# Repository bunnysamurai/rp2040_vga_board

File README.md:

# Intro
A modified version of the RP2040 vga support board from Raspberry Pi.

Source VGA board can be found [here](https://datasheets.raspberrypi.com/rp2040/VGA-KiCAD.zip).

As a design goal, this board is intended to support all the features made available from the [RP2040 DOOM](https://kilograham.github.io/rp2040-doom/) project:
- Keyboard input
- Full colour VGA
- Original(ish) sound
- Multiplayer (over I2C)

# Tools
KiCad: version 6.0.9, at least

Design rules follow [those documented by PCBWay](https://www.pcbway.com/capabilities.html)

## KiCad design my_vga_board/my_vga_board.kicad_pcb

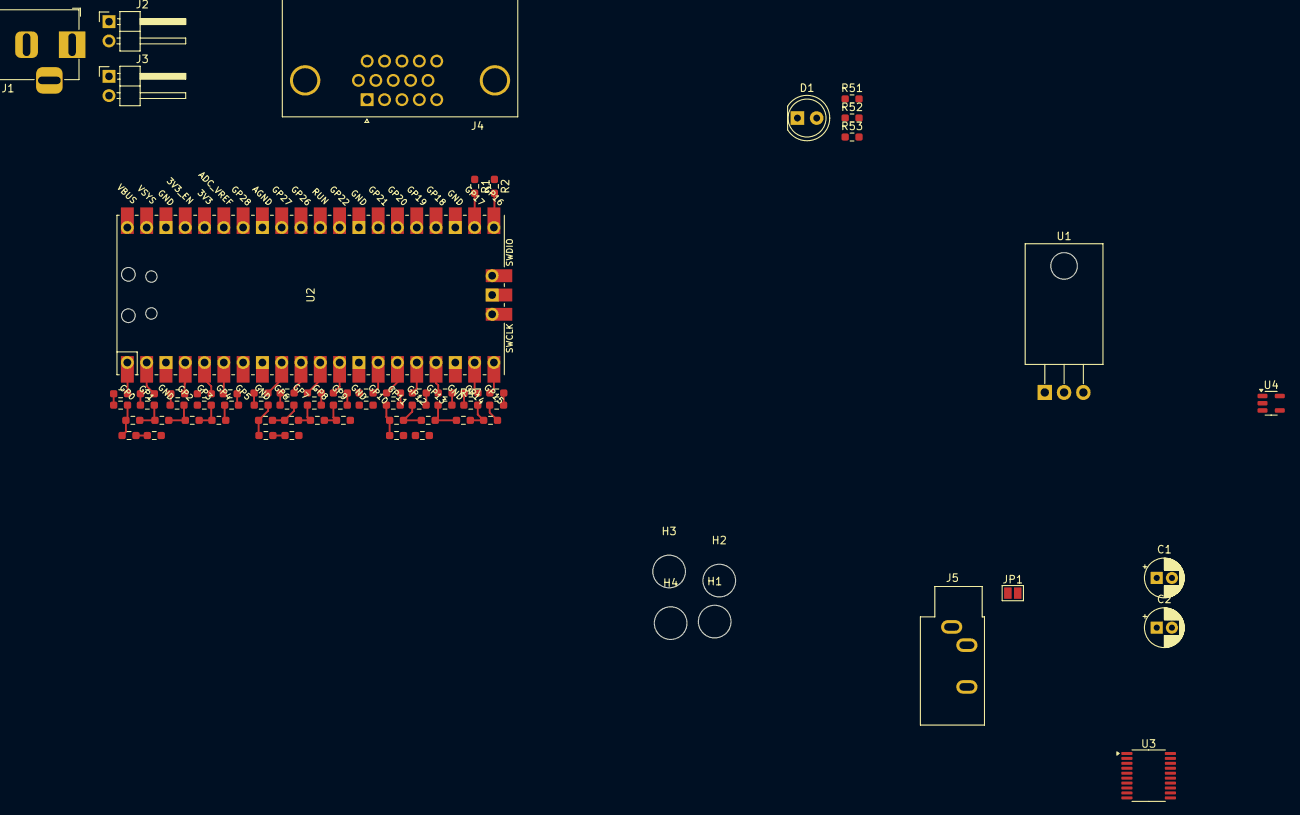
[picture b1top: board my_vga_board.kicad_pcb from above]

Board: 2 copper layers, 70 parts (0 on the bottom side), 67 nets.

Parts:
C1: 0.33uF; CP_Radial_D5.0mm_P2.00mm
C2: 0.1uF; CP_Radial_D5.0mm_P2.00mm
D1: LED; LED_D5.0mm
H1, H2, H3, H4: MountingHole; MountingHole_4.3mm_M4
J1: Barrel_Jack; BarrelJack_Horizontal
J2: I2C_A; PinHeader_1x02_P2.54mm_Horizontal
J3: I2C_B; PinHeader_1x02_P2.54mm_Horizontal
J4: L77HDE15SD1CH4F; DSUB-15-L77HDE15SD1CH4F
J5: AudioJack2_Ground; Jack_3.5mm_CUI_SJ1-3533NG_Horizontal
JP1: Open; SolderJumper-2_P1.3mm_Open_Pad1.0x1.5mm
R1, R2: 47; R_0603_1608Metric_Pad0.98x0.95mm_HandSolder
R3, R4, R5, R6, R7, R8, R9, R10, R11, R12, R13, R14, R15, R16, R17, R18, R19, R20, R21, R22, R23, R24, R25, R26, R27, R28, R29, R30, R31, R32, R33, R34, R35, R36, R37, R38, R39, R40, R41, R42, R43, R44, R45, R46, R47, R48, R49, R50: R; R_0603_1608Metric_Pad0.98x0.95mm_HandSolder
R51, R52: 470; R_0603_1608Metric_Pad0.98x0.95mm_HandSolder
R53: 330; R_0603_1608Metric_Pad0.98x0.95mm_HandSolder
U1: LM7805_TO220; TO-220-3_Horizontal_TabDown
U2: Pico; RPi_Pico_SMD_TH
U3: PCM5101A; TSSOP-20_4.4x6.5mm_P0.65mm
U4: LD3985M33R_SOT23; SOT-23-5

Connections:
+3V3 (OUT): U2.36 (3V3), U3.17 (XSMT), U3.20 (DVDD)
+5V: C2.1, JP1.2 (B), R53.1, U1.3 (VO), U2.39 (VSYS), U4.1 (VIN), U4.3 (INH)
/GPIO0: R3.1, U2.1 (GPIO0)
/GPIO1: R13.1, U2.2 (GPIO1)
/GPIO2: R19.1, U2.4 (GPIO2)
/GPIO3: R25.1, U2.5 (GPIO3)
/GPIO4: R31.1, U2.6 (GPIO4)
/GPIO6: R7.1, U2.9 (GPIO6)
/GPIO7: R15.1, U2.10 (GPIO7)
/GPIO8: R21.1, U2.11 (GPIO8)
/GPIO9: R27.1, U2.12 (GPIO9)
/GPIO10: R33.1, U2.14 (GPIO10)
/GPIO11: R35.1, U2.15 (GPIO11)
/GPIO12: R40.1, U2.16 (GPIO12)
/GPIO13: R43.1, U2.17 (GPIO13)
/GPIO14: R46.1, U2.19 (GPIO14)
/GPIO15: R49.1, U2.20 (GPIO15)
/GPIO26: U2.31 (GPIO26_ADC0), U3.15 (LRCK)
/GPIO27: U2.32 (GPIO27_ADC1), U3.13 (BCK)
/GPIO28: U2.34 (GPIO28_ADC2), U3.14 (DIN)
/HSYNC: R1.1, U2.21 (GPIO16)
/SCL: J2.1, J3.1, U2.25 (GPIO19)
/SDA: J2.2, J3.2, U2.24 (GPIO18)
/VGA_B: J4.3, R48.2, R50.2
/VGA_G: J4.2, R30.2, R34.2
/VGA_R: J4.1, R29.2, R32.2
/VSYNC: R2.1, U2.22 (GPIO17)
GND: C1.2, C2.2, D1.1 (K), J1.2, J4.0, J4.5, J4.6, J4.7, J4.8, J4.10, R6.2, R10.2, R38.2, U1.2 (GND), U2.3 (GND), U2.8 (GND), U2.13 (GND), U2.18 (GND), U2.23 (GND), U2.28 (GND), U2.33 (AGND), U2.38 (GND), U2.42 (GND), U3.1 (CPVDD), U3.3 (CPGND), U3.8 (AVDD), U3.9 (AGND), U3.10 (DEMP), U3.11 (FLT), U3.12 (SCK), U3.16 (FMT), U3.19 (DGND), U4.2 (GND)
unnamed: J5.S, R52.1
unnamed: J5.T, R51.2
unnamed: D1.2 (A), R53.2
unnamed: J4.13, R1.2
unnamed: J4.14, R2.2
unnamed: JP1.1 (A), U2.40 (VBUS)
unnamed: R3.2, R4.1
unnamed: R5.2, R6.1
unnamed: R7.2, R8.1
unnamed: R9.2, R10.1
unnamed: R4.2, R5.1, R11.1
unnamed: R11.2, R14.2, R17.1
unnamed: R8.2, R9.1, R12.1
unnamed: R12.2, R16.2, R18.1
unnamed: R13.2, R14.1
unnamed: R15.2, R16.1
unnamed: R17.2, R20.2, R23.1
unnamed: R18.2, R22.2, R24.1
unnamed: R19.2, R20.1
unnamed: R21.2, R22.1
unnamed: R23.2, R26.2, R29.1
unnamed: R24.2, R28.2, R30.1
unnamed: R25.2, R26.1
unnamed: R27.2, R28.1
unnamed: R31.2, R32.1
unnamed: R33.2, R34.1
unnamed: R35.2, R36.1
unnamed: R36.2, R37.1, R39.1
unnamed: R37.2, R38.1
unnamed: R39.2, R41.2, R42.1
unnamed: R40.2, R41.1
unnamed: R42.2, R44.2, R45.1
unnamed: R43.2, R44.1
unnamed: R45.2, R47.2, R48.1
unnamed: R46.2, R47.1
unnamed: R49.2, R50.1
unnamed: R51.1, U3.6 (OUTL)
unnamed: R52.2, U3.7 (OUTR)
VIN: C1.1, J1.1, U1.1 (VI)

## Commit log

2022-11-30 updated commit
2022-11-30 adding power circuit, some layout schtuff
2022-12-06 updated kicad symbol lib version
2022-12-07 I don't know, some changes?
2022-12-07 ignore backups, and other things!
2022-12-07 more ignoring
2022-12-07 adding stubs for schematic comments section
2022-12-19 better footprints for resistance
2022-12-22 adding tracks! Neat
2022-12-22 adding version info for kicad to readme
2023-01-05 now supports multiplayer... over I2C?
2023-01-05 readme updates!
2023-01-06 maybe can be fabbed?
2023-01-06 add mention of the source for the design rules
2023-01-06 now with mounting holes, and accredidation, ooooh
2023-01-09 gerber files?
2023-01-16 comment change. I really need to get this board ordered!
2024-07-17 R-2R
2024-08-09 some sound

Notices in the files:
my_vga_board/my_vga_board.kicad_pcb:
License: MIT
